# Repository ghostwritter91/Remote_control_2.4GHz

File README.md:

1. Remote control using EFM32ZG110F32-QFN24T and NRF24L01
2. PCBs for receiver and transmitter in KiCAD.
3. Software projects in Simplicity Studio v3.

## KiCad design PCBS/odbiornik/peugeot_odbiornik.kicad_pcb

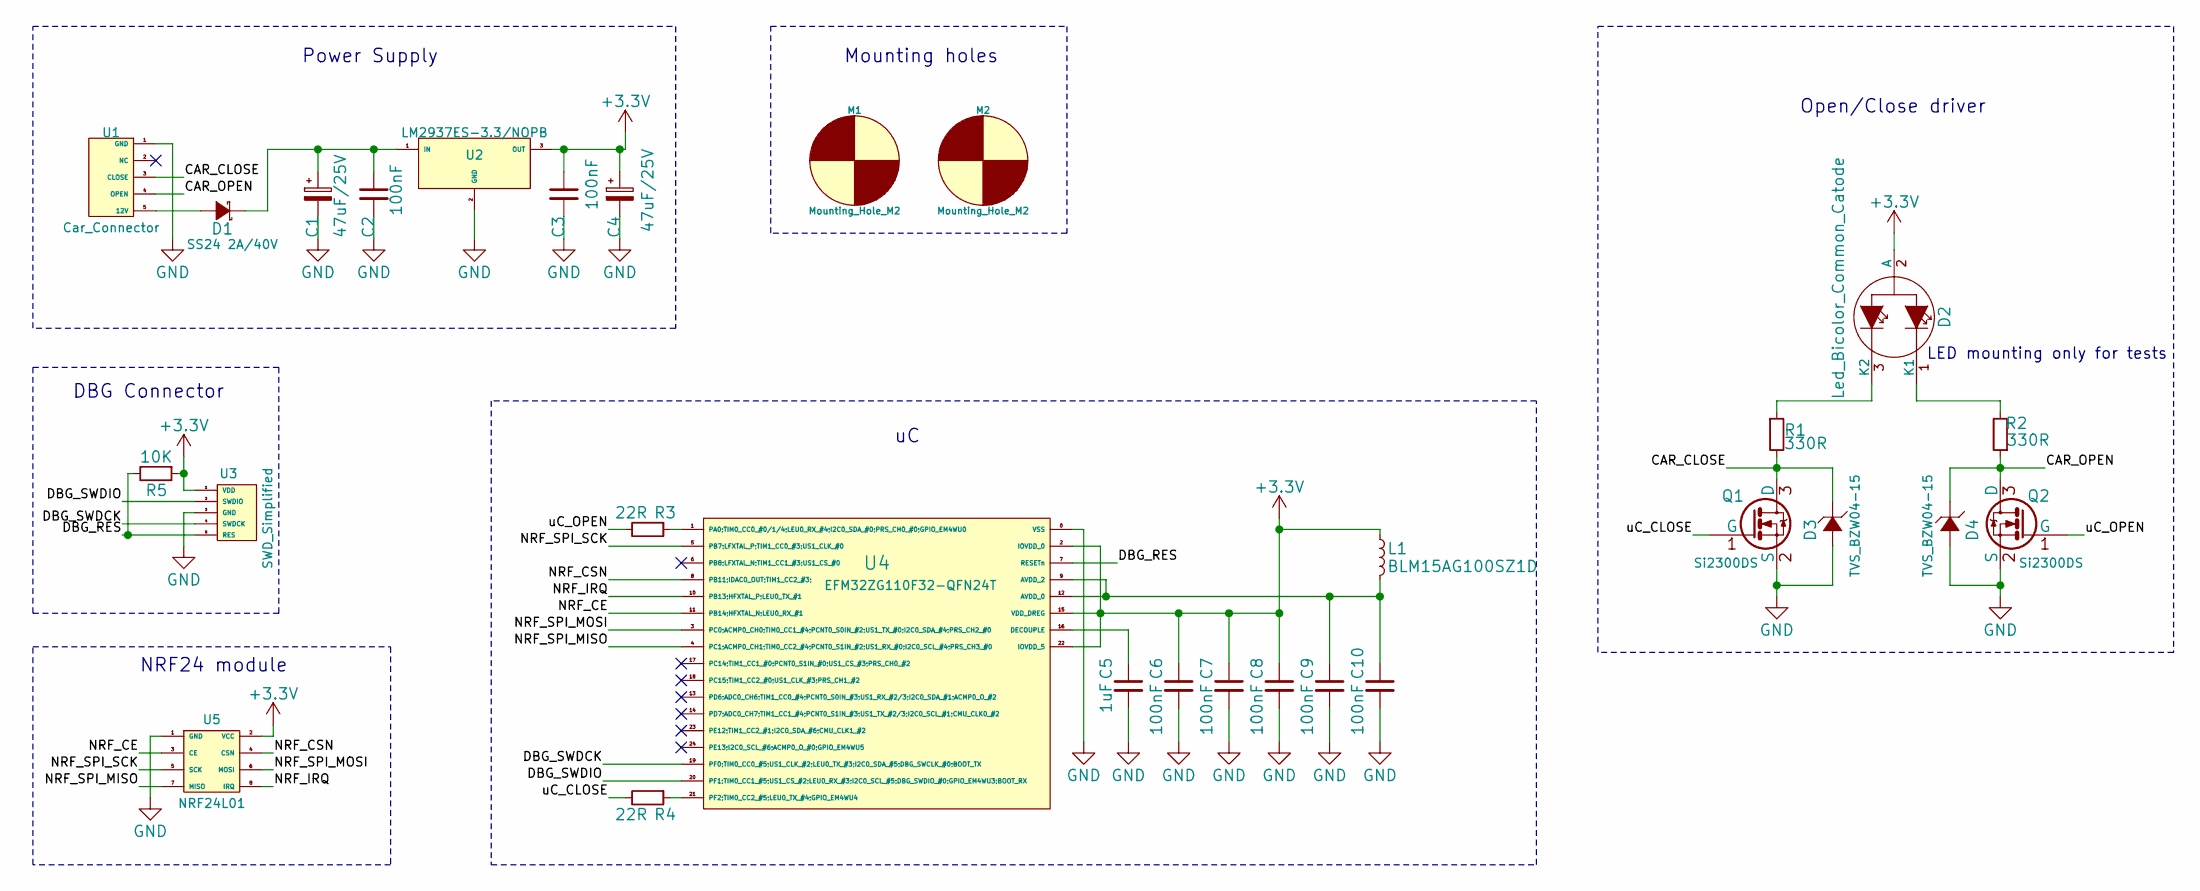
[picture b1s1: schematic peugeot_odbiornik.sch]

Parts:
C1, C4: 47uF/25V; C_Radial_D5_L11_P2.5
C2, C3, C6, C7, C8, C9, C10: 100nF; CNSN_C_0402
C5: 1uF; CNSN_C_0402
D1: SS24 2A/40V; CNSN_DO_214AC
D2: Led_Bicolor_Common_Catode; LED_3ARG9HWA
D3, D4: TVS_BZW04-15; DO-15
L1: BLM15AG100SZ1D; CNSN_L_0402
M1, M2: Mounting_Hole_M2; Mounting_Hole_2mm
Q1, Q2: Si2300DS; SOT-23
R1, R2: 330R; R_0603_HandSoldering
R3, R4: 22R; R_0603_HandSoldering
R5: 10K; CNSN_R_0402
U1: Car_Connector; Connector_RX
U2: LM2937ES-3.3/NOPB; TO-263
U3: SWD_Simplified; CNSN_SWD_SimplifiedConnector(pitch1.27)
U4: EFM32ZG110F32-QFN24T; QFN-24-1EP_5x5mm_Pitch0.65mm
U5: NRF24L01

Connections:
+3V3: C3.1, C4.1, C6.1, C7.1, C8.1, D2.2 (A), L1.1, R5.1, U2.3 (OUT), U3.1 (VDD), U4.2 (IOVDD_0), U4.15 (VDD_DREG), U4.22 (IOVDD_5), U5.2 (VCC)
/CAR_CLOSE: D3.1 (K), Q1.3 (D), R1.2, U1.3 (CLOSE)
/CAR_OPEN: D4.1 (K), Q2.3 (D), R2.1, U1.4 (OPEN)
/DBG_RES: R5.2, U3.5 (RES), U4.7 (RESETn)
/DBG_SWDCK: U3.4 (SWDCK), U4.19 (PF0;TIM0_CC0_#5;US1_CLK_#2;LEU0_TX_#3;I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)
/DBG_SWDIO: U3.2 (SWDIO), U4.20 (PF1;TIM0_CC1_#5;US1_CS_#2;LEU0_RX_#3;I2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)
/NRF_CE: U4.11 (PB14;HFXTAL_N;LEU0_RX_#1), U5.3 (CE)
/NRF_CSN: U4.8 (PB11;IDAC0_OUT;TIM1_CC2_#3;), U5.4 (CSN)
/NRF_IRQ: U4.10 (PB13;HFXTAL_P;LEU0_TX_#1), U5.8 (IRQ)
/NRF_SPI_MISO: U4.4 (PC1;ACMP0_CH1;TIM0_CC2_#4;PCNT0_S1IN_#2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), U5.7 (MISO)
/NRF_SPI_MOSI: U4.3 (PC0;ACMP0_CH0;TIM0_CC1_#4;PCNT0_S0IN_#2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), U5.6 (MOSI)
/NRF_SPI_SCK: U4.5 (PB7;LFXTAL_P;TIM1_CC0_#3;US1_CLK_#0), U5.5 (SCK)
/uC_CLOSE: Q1.1 (G), R4.2
/uC_OPEN: Q2.1 (G), R3.2
GND: C1.2, C2.2, C3.2, C4.2, C5.2, C6.2, C7.2, C8.2, C9.2, C10.2, D3.2 (A), D4.2 (A), Q1.2 (S), Q2.2 (S), U1.1 (GND), U2.2 (GND), U3.3 (GND), U4.0 (VSS), U5.1 (GND)
unnamed: C1.1, C2.1, D1.1 (K), U2.1 (IN)
unnamed: C5.1, U4.16 (DECOUPLE)
unnamed: C9.1, C10.1, L1.2, U4.9 (AVDD_2), U4.12 (AVDD_0)
unnamed: D1.2 (A), U1.5 (12V)
unnamed: D2.1 (K1), R2.2
unnamed: D2.3 (K2), R1.1
unnamed: R3.1, U4.1 (PA0;TIM0_CC0_#0/1/4;LEU0_RX_#4;I2C0_SDA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)
unnamed: R4.1, U4.21 (PF2;TIM0_CC2_#5;LEU0_TX_#4;GPIO_EM4WU4)

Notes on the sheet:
Power Supply
DBG Connector
NRF24 module
Mounting holes
Open/Close driver
LED mounting only for tests

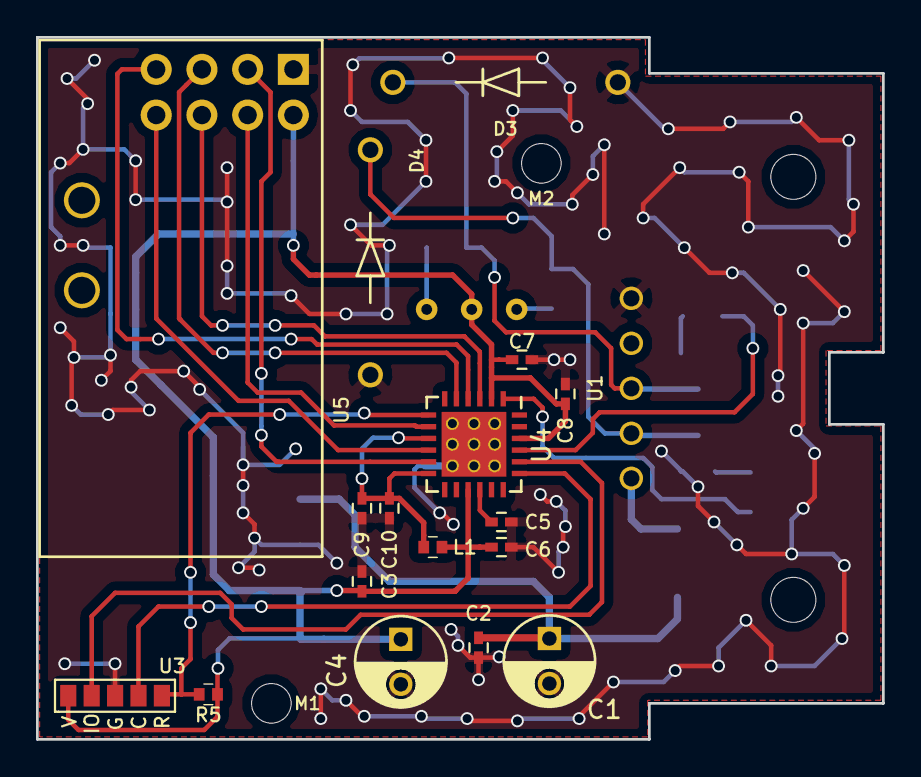
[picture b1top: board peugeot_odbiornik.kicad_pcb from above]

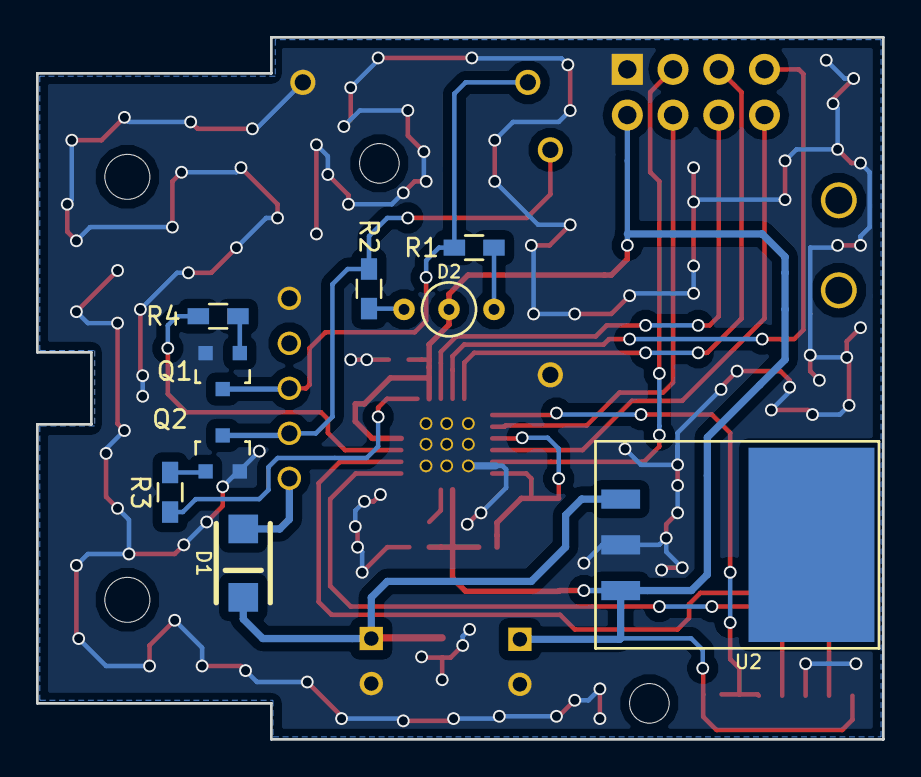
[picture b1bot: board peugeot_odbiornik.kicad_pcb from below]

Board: 2 copper layers, 47.0 x 39.0 mm, 29 parts (9 on the bottom side), 23 nets.

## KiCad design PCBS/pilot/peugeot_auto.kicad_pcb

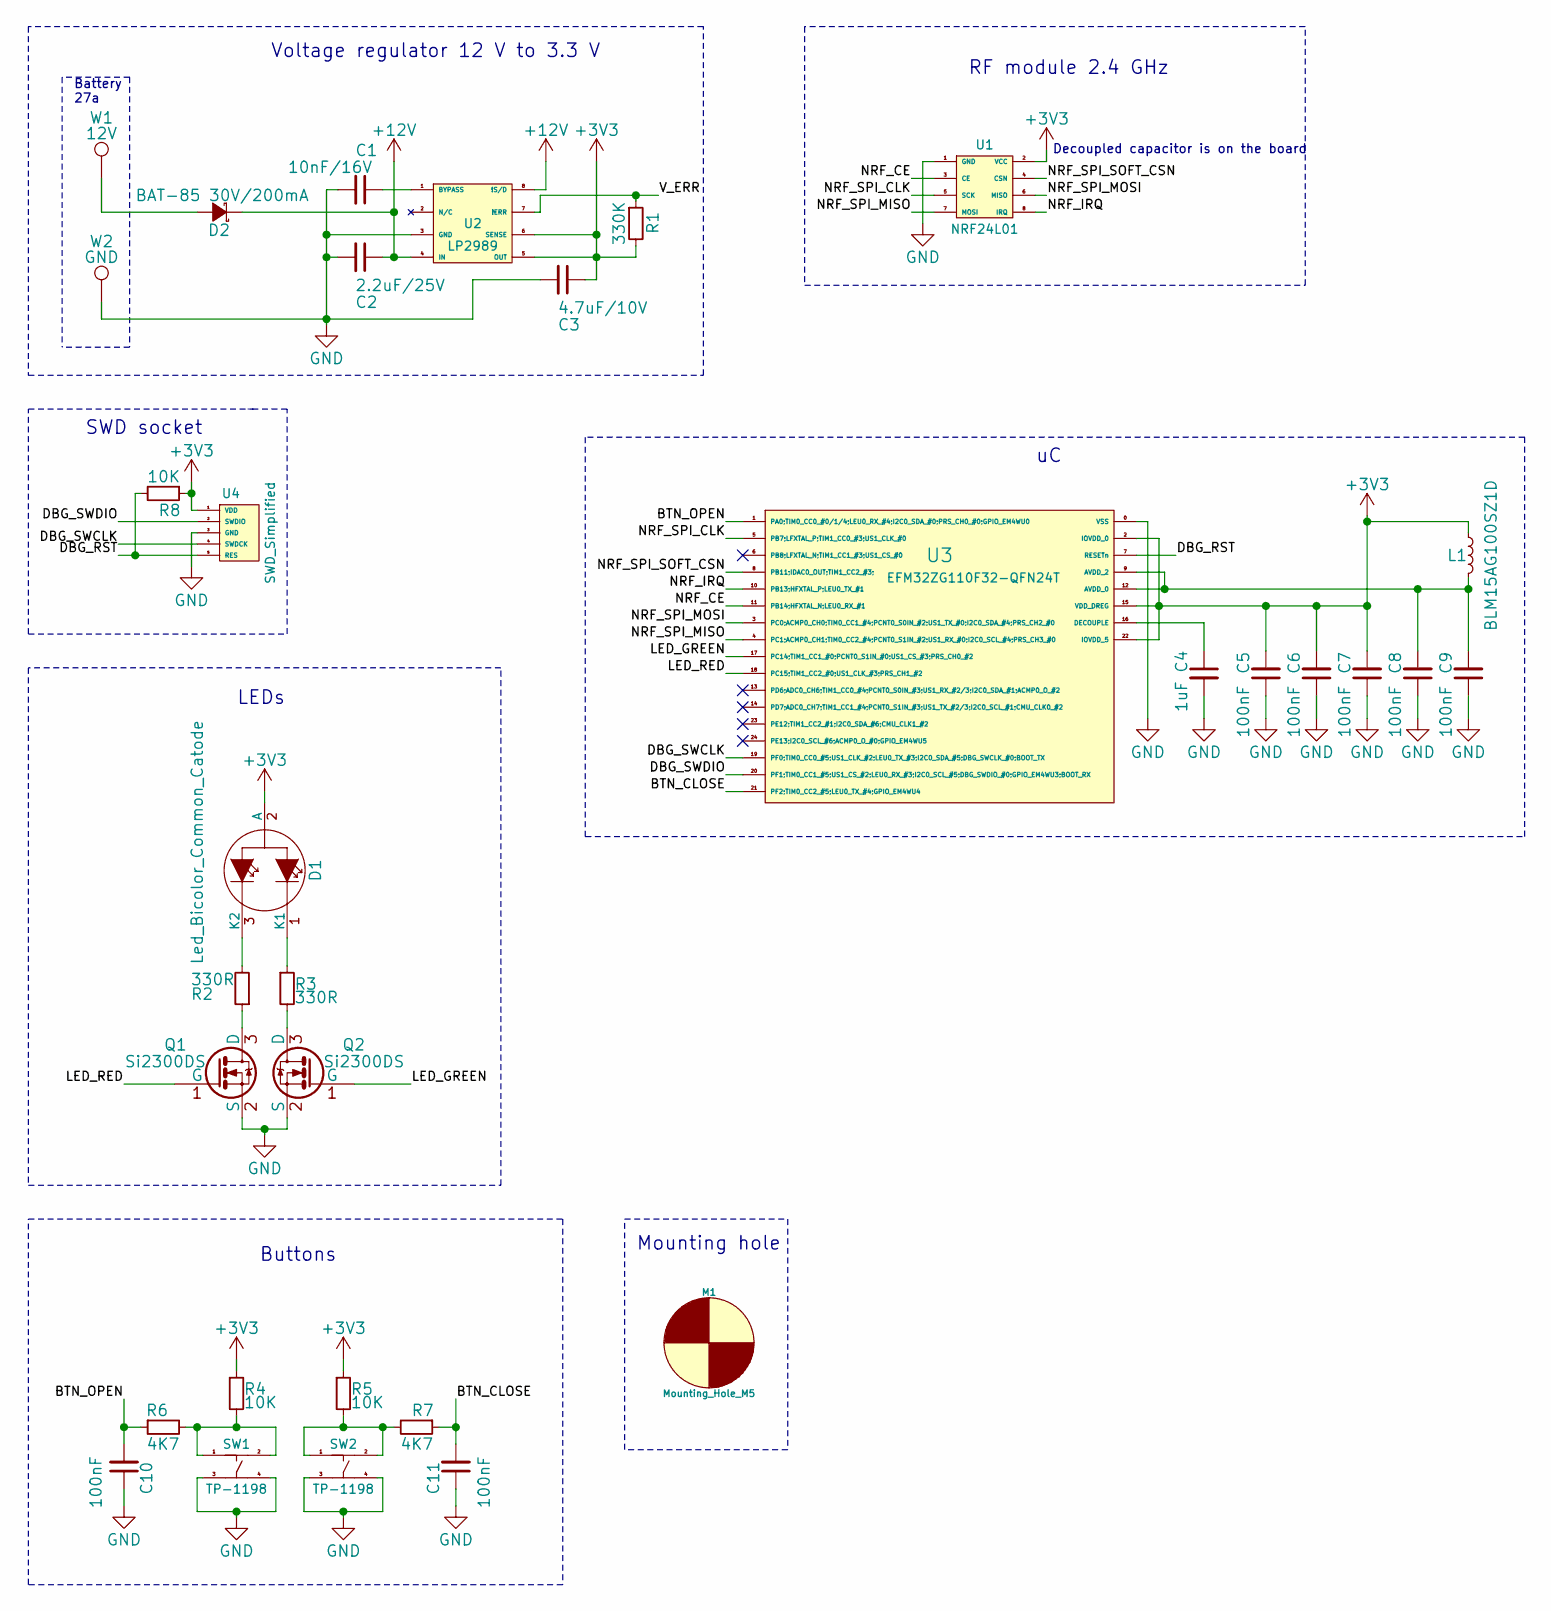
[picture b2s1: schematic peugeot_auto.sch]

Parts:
C1: 10nF/16V; CNSN_C_0402
C2: 2.2uF/25V; CNSN_C_0402
C3: 4.7uF/10V; CNSN_C_0402
C4: 1uF; CNSN_C_0402
C5, C6, C7, C8, C9, C10, C11: 100nF; CNSN_C_0402
D1: Led_Bicolor_Common_Catode; LED_3ARG9HWA
D2: BAT-85 30V/200mA; DO-34_(SOD68)
L1: BLM15AG100SZ1D; CNSN_L_0402
M1: Mounting_Hole_M5; MountingHole_5.3mm_M5
Q1, Q2: Si2300DS; SOT-23
R1: 330K; R_0805
R2, R3: 330R; R_0603_HandSoldering
R4, R5, R8: 10K; CNSN_C_0402
R6, R7: 4K7; CNSN_C_0402
SW1, SW2: TP-1198; TP-1198_4.5x4.5x0.55mm
U1: NRF24L01
U2: LP2989; VSSOP8
U3: EFM32ZG110F32-QFN24T; QFN-24-1EP_5x5mm_Pitch0.65mm
U4: SWD_Simplified; CNSN_SWD_SimplifiedConnector(pitch1.27)
W1: 12V; Measurement_Point_Square-SMD-Pad_Small
W2: GND; Measurement_Point_Square-SMD-Pad_Small

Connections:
+3V3: C3.1, C5.2, C6.2, C7.2, D1.2 (A), L1.1, R1.2, R4.1, R5.1, R8.1, U1.2 (VCC), U2.5 (OUT), U2.6 (SENSE), U3.2 (IOVDD_0), U3.15 (VDD_DREG), U3.22 (IOVDD_5), U4.1 (VDD)
+12V: C2.1, D2.1 (K), U2.4 (IN), U2.8 (!S/D)
/BTN_CLOSE: C11.2, R7.1, U3.21 (PF2;TIM0_CC2_#5;LEU0_TX_#4;GPIO_EM4WU4)
/BTN_OPEN: C10.2, R6.1, U3.1 (PA0;TIM0_CC0_#0/1/4;LEU0_RX_#4;I2C0_SDA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)
/DBG_RST: R8.2, U3.7 (RESETn), U4.5 (RES)
/DBG_SWCLK: U3.19 (PF0;TIM0_CC0_#5;US1_CLK_#2;LEU0_TX_#3;I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), U4.4 (SWDCK)
/DBG_SWDIO: U3.20 (PF1;TIM0_CC1_#5;US1_CS_#2;LEU0_RX_#3;I2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), U4.2 (SWDIO)
/LED_GREEN: Q2.1 (G), U3.17 (PC14;TIM1_CC1_#0;PCNT0_S1IN_#0;US1_CS_#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)
/LED_RED: Q1.1 (G), U3.18 (PC15;TIM1_CC2_#0;US1_CLK_#3;PRS_CH1_#2)
/NRF_CE: U1.3 (CE), U3.11 (PB14;HFXTAL_N;LEU0_RX_#1)
/NRF_IRQ: U1.8 (IRQ), U3.10 (PB13;HFXTAL_P;LEU0_TX_#1)
/NRF_SPI_CLK: U1.5 (SCK), U3.5 (PB7;LFXTAL_P;TIM1_CC0_#3;US1_CLK_#0)
/NRF_SPI_MISO: U1.7 (MOSI), U3.4 (PC1;ACMP0_CH1;TIM0_CC2_#4;PCNT0_S1IN_#2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)
/NRF_SPI_MOSI: U1.6 (MISO), U3.3 (PC0;ACMP0_CH0;TIM0_CC1_#4;PCNT0_S0IN_#2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)
/NRF_SPI_SOFT_CSN: U1.4 (CSN), U3.8 (PB11;IDAC0_OUT;TIM1_CC2_#3;)
/V_ERR: R1.1, U2.7 (!ERR)
GND: C1.2, C2.2, C3.2, C4.2, C5.1, C6.1, C7.1, C8.1, C9.1, C10.1, C11.1, Q1.2 (S), Q2.2 (S), SW1.3, SW1.4, SW2.3, SW2.4, U1.1 (GND), U2.3 (GND), U3.0 (VSS), U4.3 (GND), W2.1
unnamed: C1.1, U2.1 (BYPASS)
unnamed: C4.1, U3.16 (DECOUPLE)
unnamed: C8.2, C9.2, L1.2, U3.9 (AVDD_2), U3.12 (AVDD_0)
unnamed: D1.1 (K1), R3.1
unnamed: D1.3 (K2), R2.2
unnamed: D2.2 (A), W1.1
unnamed: Q1.3 (D), R2.1
unnamed: Q2.3 (D), R3.2
unnamed: R4.2, R6.2, SW1.1, SW1.2
unnamed: R5.2, R7.2, SW2.1, SW2.2

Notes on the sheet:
Battery 27a
Decoupled capacitor is on the board
Buttons
LEDs
Mounting hole
SWD socket
RF module 2.4 GHz
Voltage regulator 12 V to 3.3 V

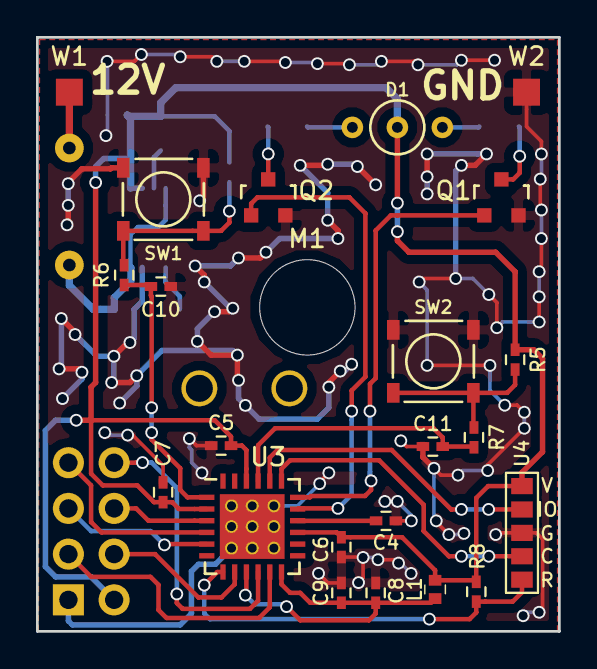
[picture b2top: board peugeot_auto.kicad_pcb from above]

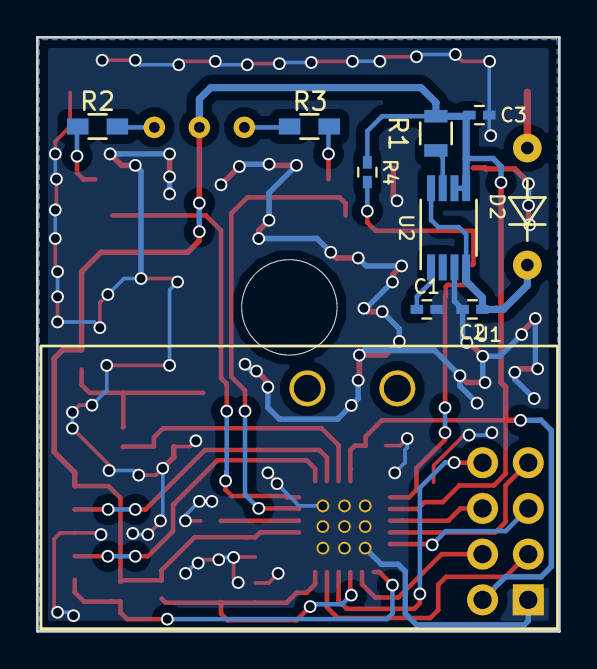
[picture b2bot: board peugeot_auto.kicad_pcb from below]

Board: 2 copper layers, 29.0 x 33.0 mm, 33 parts (10 on the bottom side), 27 nets.

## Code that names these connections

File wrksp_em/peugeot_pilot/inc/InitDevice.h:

//=========================================================
// inc/InitDevice.h: generated by Hardware Configurator
//
// This file will be regenerated when saving a document.
// leave the sections inside the "$[...]" comment tags alone
// or they will be overwritten!
//=========================================================
#ifndef __INIT_DEVICE_H__
#define __INIT_DEVICE_H__

// USER CONSTANTS
// USER PROTOTYPES

// $[Mode Transition Prototypes]
extern void enter_DefaultMode_from_RESET(void);
// [Mode Transition Prototypes]$

// $[Config(Per-Module Mode)Transition Prototypes]
extern void HFXO_enter_DefaultMode_from_RESET(void);
extern void LFXO_enter_DefaultMode_from_RESET(void);
extern void CMU_enter_DefaultMode_from_RESET(void);
extern void ADC0_enter_DefaultMode_from_RESET(void);
extern void ACMP0_enter_DefaultMode_from_RESET(void);
extern void IDAC0_enter_DefaultMode_from_RESET(void);
extern void RTC_enter_DefaultMode_from_RESET(void);
extern void USART1_enter_DefaultMode_from_RESET(void);
extern void LEUART0_enter_DefaultMode_from_RESET(void);
extern void VCMP_enter_DefaultMode_from_RESET(void);
extern void WDOG_enter_DefaultMode_from_RESET(void);
extern void I2C0_enter_DefaultMode_from_RESET(void);
extern void TIMER0_enter_DefaultMode_from_RESET(void);
extern void TIMER1_enter_DefaultMode_from_RESET(void);
extern void PCNT0_enter_DefaultMode_from_RESET(void);
extern void PRS_enter_DefaultMode_from_RESET(void);
extern void PORTIO_enter_DefaultMode_from_RESET(void);
// [Config(Per-Module Mode)Transition Prototypes]$

// $[User-defined pin name abstraction]

#define BTN_CLOSE_PIN               (2)
#define BTN_CLOSE_PORT              (gpioPortF)

#define BTN_OPEN_PIN                (0)
#define BTN_OPEN_PORT               (gpioPortA)

#define GPIO_EM4WU0_PIN             (0)
#define GPIO_EM4WU0_PORT            (gpioPortA)

#define GPIO_EM4WU4_PIN             (2)
#define GPIO_EM4WU4_PORT            (gpioPortF)

#define LED_GREEN_PIN               (14)
#define LED_GREEN_PORT              (gpioPortC)

#define LED_RED_PIN                 (15)
#define LED_RED_PORT                (gpioPortC)

#define NC_13_PIN                   (6)
#define NC_13_PORT                  (gpioPortD)

#define NC_14_PIN                   (7)
#define NC_14_PORT                  (gpioPortD)

#define NC_23_PIN                   (12)
#define NC_23_PORT                  (gpioPortE)

#define NC_24_PIN                   (13)
#define NC_24_PORT                  (gpioPortE)

#define NC_6_PIN                    (8)
#define NC_6_PORT                   (gpioPortB)

#define NRF_CE_PIN                  (14)
#define NRF_CE_PORT                 (gpioPortB)

#define NRF_IRQ_PIN                 (13)
#define NRF_IRQ_PORT                (gpioPortB)

#define NRF_SPI_CLK_PIN             (7)
#define NRF_SPI_CLK_PORT            (gpioPortB)

#define NRF_SPI_MISO_PIN            (1)
#define NRF_SPI_MISO_PORT           (gpioPortC)

#define NRF_SPI_MOSI_PIN            (0)
#define NRF_SPI_MOSI_PORT           (gpioPortC)

#define NRF_SPI_SOFT_CSN_PIN        (11)
#define NRF_SPI_SOFT_CSN_PORT       (gpioPortB)

// [User-defined pin name abstraction]$

#endif

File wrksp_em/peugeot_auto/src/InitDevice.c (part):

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
	// $[Port A Configuration]

	/* Pin PA0 is configured to Push-pull */
	GPIO->P[0].MODEL = (GPIO->P[0].MODEL & ~_GPIO_P_MODEL_MODE0_MASK)
			| GPIO_P_MODEL_MODE0_PUSHPULL;
	// [Port A Configuration]$

	// $[Port B Configuration]

	/* Pin PB7 is configured to Push-pull */
	GPIO->P[1].MODEL = (GPIO->P[1].MODEL & ~_GPIO_P_MODEL_MODE7_MASK)
			| GPIO_P_MODEL_MODE7_PUSHPULL;

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	GPIO->P[1].MODEH = (GPIO->P[1].MODEH & ~_GPIO_P_MODEH_MODE8_MASK)
			| GPIO_P_MODEH_MODE8_INPUTPULL;

	/* Pin PB11 is configured to Push-pull */
	GPIO->P[1].MODEH = (GPIO->P[1].MODEH & ~_GPIO_P_MODEH_MODE11_MASK)
			| GPIO_P_MODEH_MODE11_PUSHPULL;

	/* Pin PB13 is configured to Input enabled with filter */
	GPIO->P[1].DOUT |= (1 << 13);
	GPIO->P[1].MODEH = (GPIO->P[1].MODEH & ~_GPIO_P_MODEH_MODE13_MASK)
			| GPIO_P_MODEH_MODE13_INPUT;

	/* Pin PB14 is configured to Push-pull */
	GPIO->P[1].DOUT |= (1 << 14);
	GPIO->P[1].MODEH = (GPIO->P[1].MODEH & ~_GPIO_P_MODEH_MODE14_MASK)
			| GPIO_P_MODEH_MODE14_PUSHPULL;
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
	// $[Port C Configuration]

	/* Pin PC0 is configured to Push-pull */
	GPIO->P[2].MODEL = (GPIO->P[2].MODEL & ~_GPIO_P_MODEL_MODE0_MASK)
			| GPIO_P_MODEL_MODE0_PUSHPULL;

	/* Pin PC1 is configured to Input enabled */
	GPIO->P[2].MODEL = (GPIO->P[2].MODEL & ~_GPIO_P_MODEL_MODE1_MASK)
			| GPIO_P_MODEL_MODE1_INPUT;

	/* Pin PC14 is configured to Input enabled with pull-down */
	GPIO->P[2].MODEH = (GPIO->P[2].MODEH & ~_GPIO_P_MODEH_MODE14_MASK)
			| GPIO_P_MODEH_MODE14_INPUTPULL;

	/* Pin PC15 is configured to Input enabled with pull-down */
	GPIO->P[2].MODEH = (GPIO->P[2].MODEH & ~_GPIO_P_MODEH_MODE15_MASK)
			| GPIO_P_MODEH_MODE15_INPUTPULL;
	// [Port C Configuration]$
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
	// $[Port F Configuration]

	/* Pin PF2 is configured to Push-pull */
	GPIO->P[5].MODEL = (GPIO->P[5].MODEL & ~_GPIO_P_MODEL_MODE2_MASK)
			| GPIO_P_MODEL_MODE2_PUSHPULL;
	// [Port F Configuration]$
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
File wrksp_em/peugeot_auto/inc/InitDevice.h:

//=========================================================
// inc/InitDevice.h: generated by Hardware Configurator
//
// This file will be regenerated when saving a document.
// leave the sections inside the "$[...]" comment tags alone
// or they will be overwritten!
//=========================================================
#ifndef __INIT_DEVICE_H__
#define __INIT_DEVICE_H__

// USER CONSTANTS
// USER PROTOTYPES

// $[Mode Transition Prototypes]
extern void enter_DefaultMode_from_RESET(void);
// [Mode Transition Prototypes]$

// $[Config(Per-Module Mode)Transition Prototypes]
extern void HFXO_enter_DefaultMode_from_RESET(void);
extern void LFXO_enter_DefaultMode_from_RESET(void);
extern void CMU_enter_DefaultMode_from_RESET(void);
extern void ADC0_enter_DefaultMode_from_RESET(void);
extern void ACMP0_enter_DefaultMode_from_RESET(void);
extern void IDAC0_enter_DefaultMode_from_RESET(void);
extern void RTC_enter_DefaultMode_from_RESET(void);
extern void USART1_enter_DefaultMode_from_RESET(void);
extern void LEUART0_enter_DefaultMode_from_RESET(void);
extern void VCMP_enter_DefaultMode_from_RESET(void);
extern void WDOG_enter_DefaultMode_from_RESET(void);
extern void I2C0_enter_DefaultMode_from_RESET(void);
extern void TIMER0_enter_DefaultMode_from_RESET(void);
extern void TIMER1_enter_DefaultMode_from_RESET(void);
extern void PCNT0_enter_DefaultMode_from_RESET(void);
extern void PRS_enter_DefaultMode_from_RESET(void);
extern void PORTIO_enter_DefaultMode_from_RESET(void);
// [Config(Per-Module Mode)Transition Prototypes]$

// $[User-defined pin name abstraction]

#define NC_13_PIN               (6)
#define NC_13_PORT              (gpioPortD)

#define NC_14_PIN               (7)
#define NC_14_PORT              (gpioPortD)

#define NC_17_PIN               (14)
#define NC_17_PORT              (gpioPortC)

#define NC_18_PIN               (15)
#define NC_18_PORT              (gpioPortC)

#define NC_23_PIN               (12)
#define NC_23_PORT              (gpioPortE)

#define NC_24_PIN               (13)
#define NC_24_PORT              (gpioPortE)

#define NC_6_PIN                (8)
#define NC_6_PORT               (gpioPortB)

#define NRF_CE_PIN              (14)
#define NRF_CE_PORT             (gpioPortB)

#define NRF_CSN_PIN             (11)
#define NRF_CSN_PORT            (gpioPortB)

#define NRF_IRQ_PIN             (13)
#define NRF_IRQ_PORT            (gpioPortB)

#define NRF_SPI_MISO_PIN        (1)
#define NRF_SPI_MISO_PORT       (gpioPortC)

#define NRF_SPI_MOSI_PIN        (0)
#define NRF_SPI_MOSI_PORT       (gpioPortC)

#define NRF_SPI_SCK_PIN         (7)
#define NRF_SPI_SCK_PORT        (gpioPortB)

#define UC_CLOSE_PIN            (2)
#define UC_CLOSE_PORT           (gpioPortF)

#define UC_OPEN_PIN             (0)
#define UC_OPEN_PORT            (gpioPortA)

// [User-defined pin name abstraction]$

#endif

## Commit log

2017-10-31 fix repo
2017-10-31 Add only necessary files
2017-10-31 Add .project files to gitignore

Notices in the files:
wrksp_em/peugeot_auto/src/InitDevice.c:
$[TIMER0 CC0 init]
$[TIMER1 CC0 init]
